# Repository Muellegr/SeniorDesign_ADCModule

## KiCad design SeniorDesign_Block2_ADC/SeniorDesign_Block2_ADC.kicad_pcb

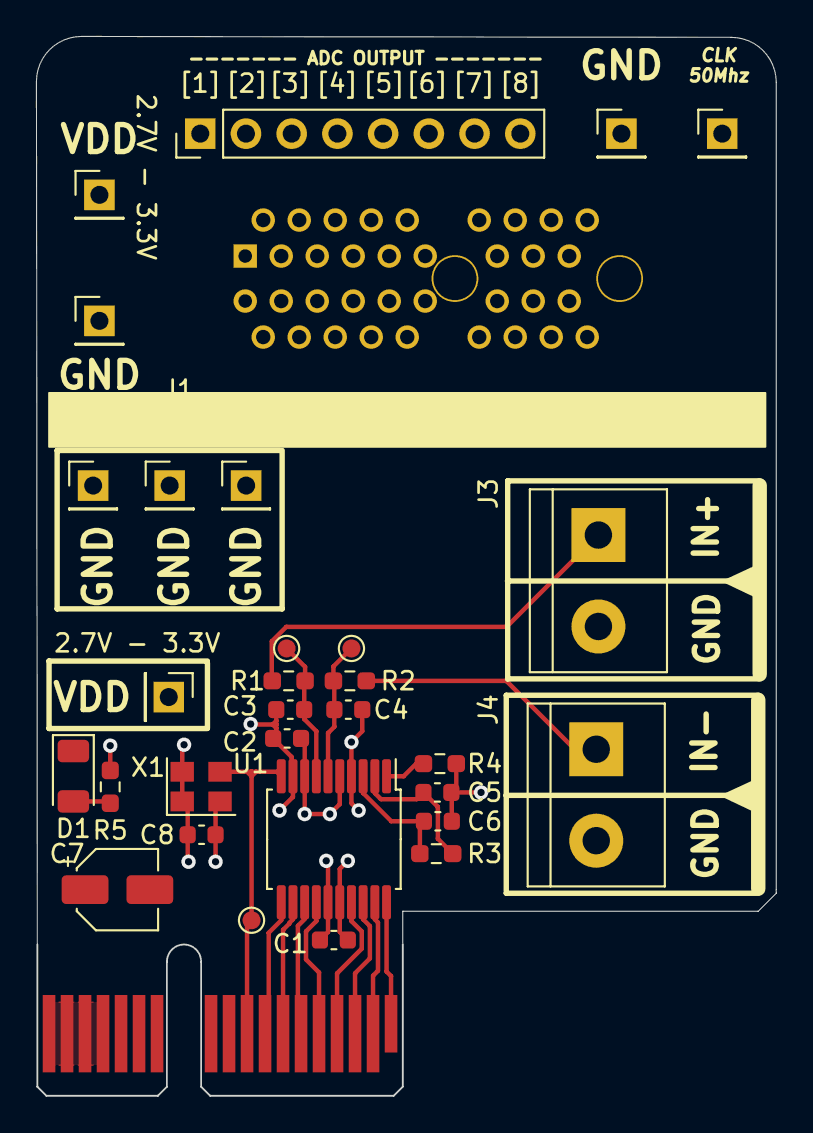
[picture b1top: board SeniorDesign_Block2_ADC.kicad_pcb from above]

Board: 4 copper layers, 41.1 x 58.8 mm, 32 parts (1 on the bottom side), 31 nets.

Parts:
C1, C2, C5, C6, C8: 0.1u; C_0603_1608Metric
C3, C4: 56pF +/-5%; C_0603_1608Metric
C7: 10u; CP_Elec_4x3.9
D1: LED; LED_1206_3216Metric
J1: Conn_02x18_Row_Letter_First; SeniorDesign_PCI_Connector
J2: Conn_02x18_Row_Letter_First; BUS_PCIexpress_x1
J3, J4: Conn_01x02_Male; TerminalBlock_bornier-2_P5.08mm
J5, J6, J7, J8, J9, J10, J12, J13: Conn_01x01; PinHeader_1x01_P2.54mm_Vertical
J11: Conn_01x08; PinHeader_1x08_P2.54mm_Vertical
R1, R2: 49.9 +/-1%; R_0603_1608Metric_Pad0.98x0.95mm_HandSolder
R3, R4: 0; R_0603_1608Metric_Pad0.98x0.95mm_HandSolder
R5: 470; R_0603_1608Metric_Pad0.98x0.95mm_HandSolder
TP1, TP2, TP4: TestPoint_Small; TestPoint_Pad_D1.0mm
U1: AD9283; SSOP-20_5.3x7.2mm_P0.65mm
X1: ASE-xxxMHz; Oscillator_SMD_Abracon_ASE-4Pin_3.2x2.5mm

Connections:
/adc_a1: J2.A1, U1.20
/adc_a2: J2.A2, U1.19
/adc_a3: J2.A3, U1.18
/adc_a4: J2.A4, U1.17
/adc_a5: J2.A5, U1.14
/adc_a6: J2.A6, U1.13
/adc_a7: J2.A7, U1.12
/adc_a8: J2.A8, U1.11
/conn_adc_a1: J1.A1, J11.1
/conn_adc_a2: J1.A2, J11.2
/conn_adc_a3: J1.A3, J11.3
/conn_adc_a4: J1.A4, J11.4
/conn_adc_a5: J1.A5, J11.5
/conn_adc_a6: J1.A6, J11.6
/conn_adc_a7: J1.A7, J11.7
/conn_adc_a8: J1.A8, J11.8
/gnd: J2.A10, J2.A11, J2.A12, J2.A13, J2.A14, J2.B1, J2.B2, J2.B3, J2.B4, J2.B5, J2.B6, J2.B7, J2.B8, J2.B9, J2.B10, J2.B11, J2.B12, J2.B13, J2.B14, J2.B15, J2.B16, J2.B17, J2.B18
GND: C1.2, C2.2, C3.2, C4.2, C5.2, C6.2, C7.2, C8.2, D1.1, J3.2, J4.2, J5.1, J6.1, J7.1, R4.2, U1.4, U1.9, U1.16, X1.2
unnamed: C3.1, R1.1, TP1.1, U1.7
unnamed: C4.1, R2.1, TP2.1, U1.6
unnamed: C5.1, R3.2, U1.2
unnamed: C6.1, R3.1, U1.3
unnamed: D1.2, R5.2
unnamed: R4.1, U1.1
clk: J2.A9, TP4.1, U1.10, X1.3
conn_clk: J1.A9, J10.1
conn_gnd: J1.A10, J1.A11, J1.A12, J1.A13, J1.A14, J1.B1, J1.B2, J1.B3, J1.B4, J1.B5, J1.B6, J1.B7, J1.B8, J1.B9, J1.B10, J1.B11, J1.B12, J1.B13, J1.B14, J1.B15, J1.B16, J1.B17, J1.B18, J12.1, J13.1
conn_vdd: J1.A15, J1.A16, J1.A17, J1.A18, J9.1
in_a+: J3.1, R1.2
in_a-: J4.1, R2.2
vdd: C1.1, C2.1, C7.1, C8.1, J2.A15, J2.A16, J2.A17, J2.A18, J8.1, R5.1, U1.5, U1.8, U1.15, X1.1, X1.4

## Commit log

2021-02-06 Added some schematic design for the connection.
2021-02-07 Added ADC, oscillator, and misc parts associated to the two
2021-02-07 Base shcematic complete. Converting to PCB with misc connection errors.
2021-02-08 Continued work. Push to github. Even worse commit messages.
